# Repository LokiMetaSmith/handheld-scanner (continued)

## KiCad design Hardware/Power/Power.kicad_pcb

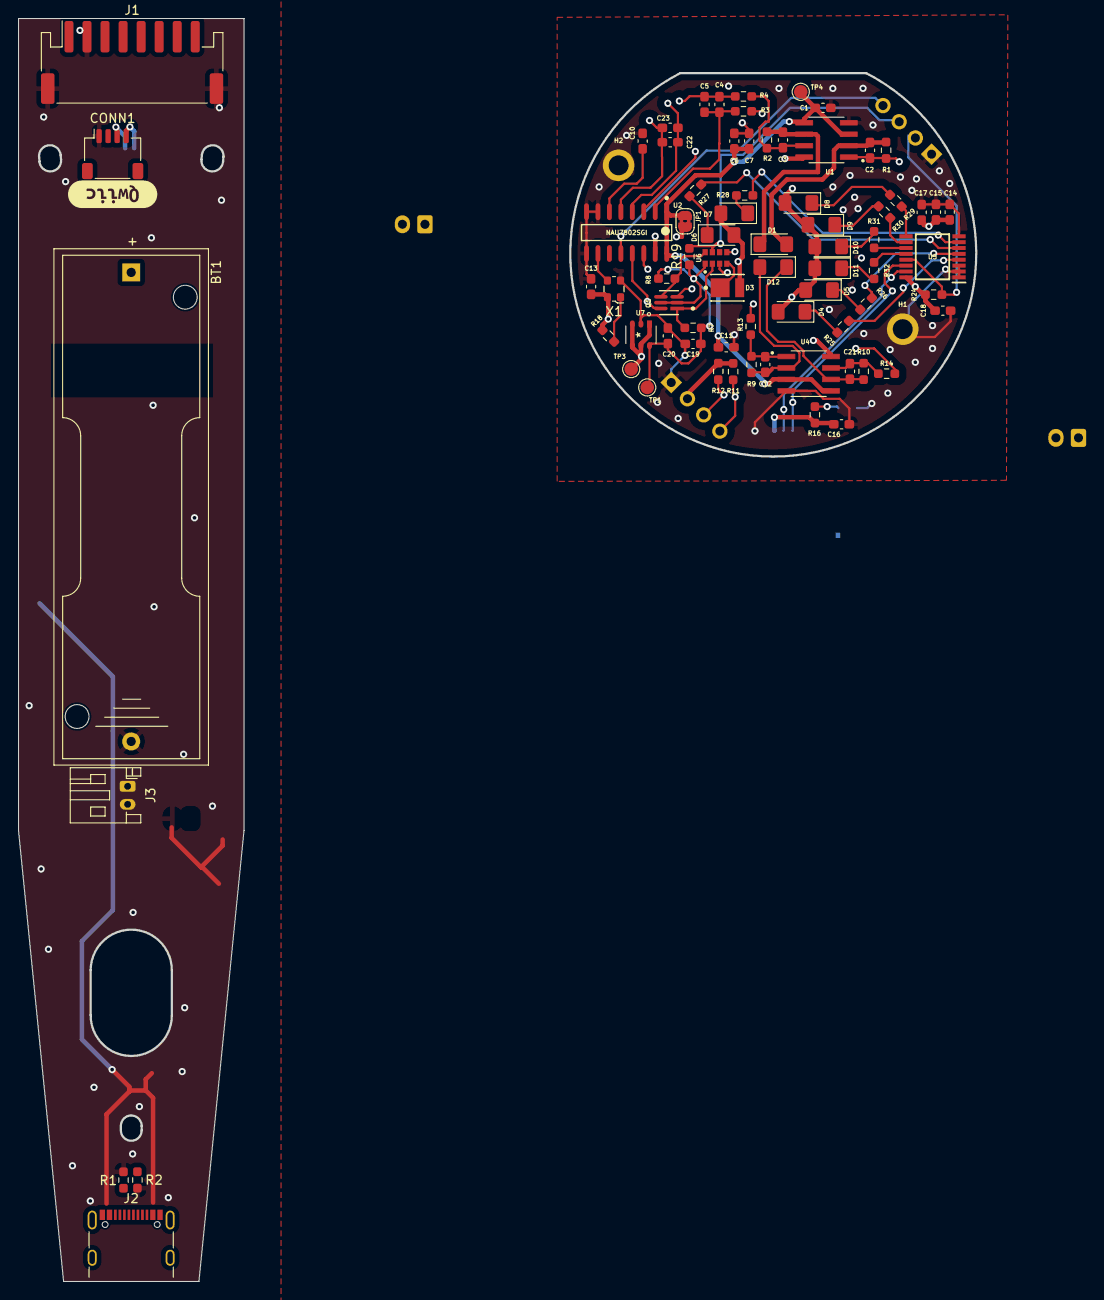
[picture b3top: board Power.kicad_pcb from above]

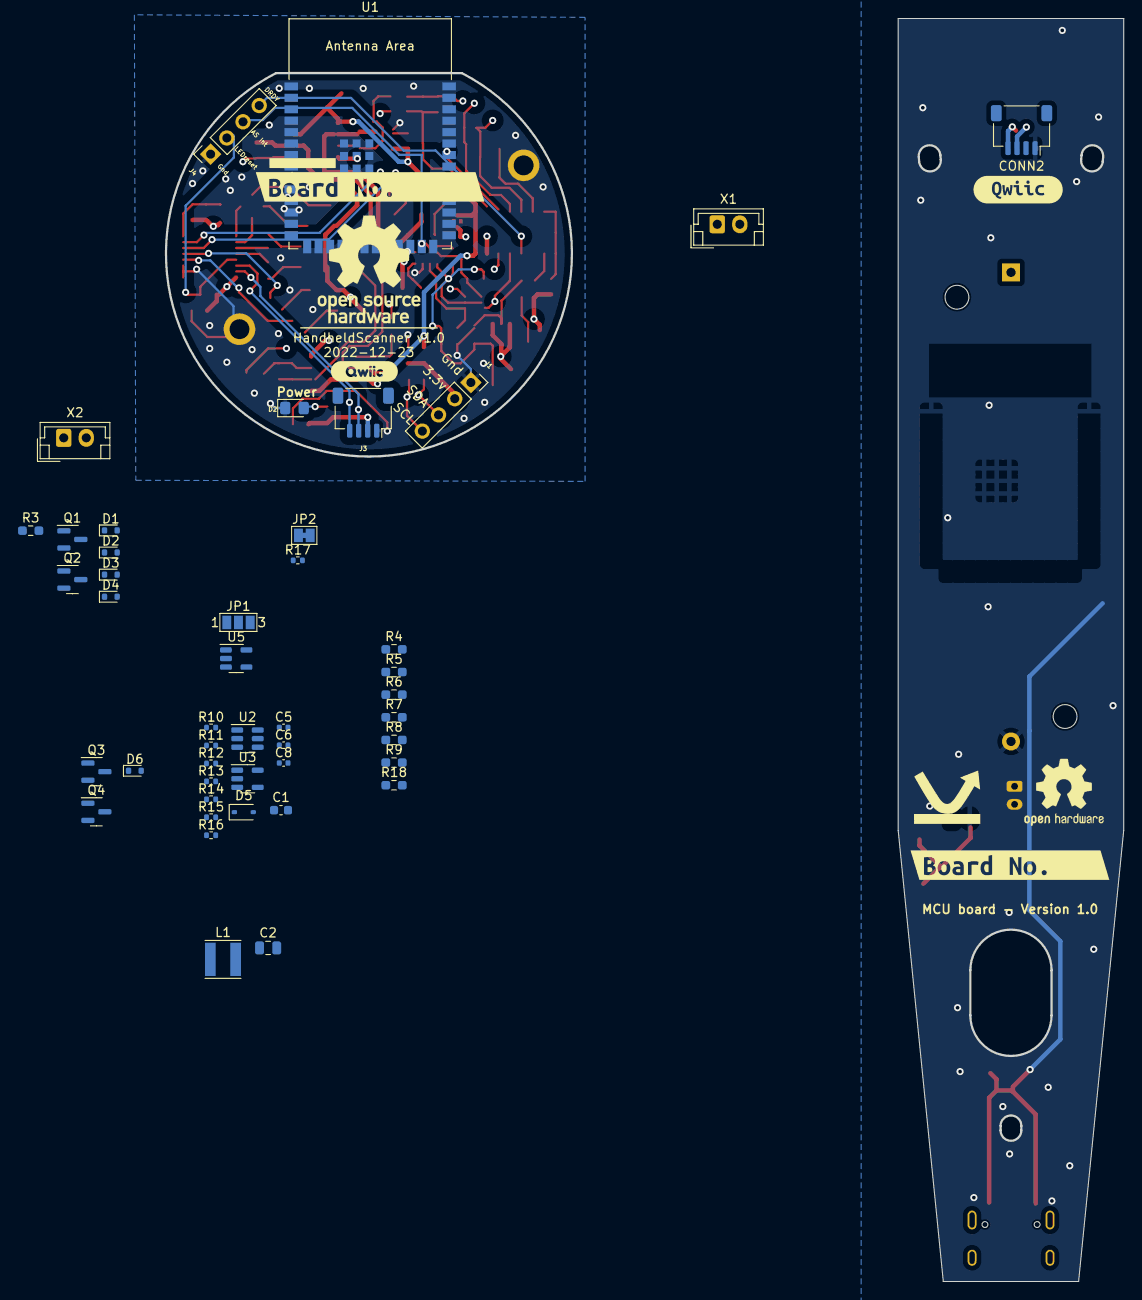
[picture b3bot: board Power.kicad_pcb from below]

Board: 4 copper layers, 106.2 x 140.0 mm, 131 parts (53 on the bottom side), 33 nets.

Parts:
BT1: Battery; BatteryHolder_Keystone_2460_1xAA
C1, C11, C16, C18: 100nF; C_0603_1608Metric_Pad1.08x0.95mm_HandSolder
C1#2: 2u; C_0603_1608Metric
C2, C3, C12, C21: 51pF; C_0603_1608Metric_Pad1.08x0.95mm_HandSolder
C2#2: 4.7u; C_0805_2012Metric
C4, C22: 47nF; C_0603_1608Metric_Pad1.08x0.95mm_HandSolder
C5, C23: 100pF; C_0603_1608Metric_Pad1.08x0.95mm_HandSolder
C5#2: 6.8p; C_0402_1005Metric
C6: 1uF; C_0603_1608Metric_Pad1.08x0.95mm_HandSolder
C6#2: 0.01u; C_0402_1005Metric
C7, C10, C13, C20: 0.1uF; C_0603_1608Metric_Pad1.08x0.95mm_HandSolder
C8: 0.1u; C_0402_1005Metric
C14, C15, C19: 10uF; C_0603_1608Metric_Pad1.08x0.95mm_HandSolder
C17: 22uF; C_0603_1608Metric_Pad1.08x0.95mm_HandSolder
CONN1, CONN2: STEMMA_I2C_QT; JST_SH_SM04B-SRSS-TB_1x04-1MP_P1.00mm_Horizontal
D1, D12: 0090-3111-185; D_1206_3216Metric_Pad1.42x1.75mm_HandSolder
D1#2, D2#2, D3#2, D4#2, D6#2: BAS516; D_SOD-523
D2: POWER LED; LED_0805_2012Metric_Pad1.15x1.40mm_HandSolder
D3: EAHC2835WD6; Everlight-EAHC2835WD6-MFG
D4: 855nm; LED_1206_3216Metric_Pad1.42x1.75mm_HandSolder
D5: 940nm; LED_1206_3216Metric_Pad1.42x1.75mm_HandSolder
D5#2: 3.3v_TVS; D_SOD-323
D6: 1050nm; LED_1206_3216Metric_Pad1.42x1.75mm_HandSolder
D7: 1300nm; LED_1206_3216Metric_Pad1.42x1.75mm_HandSolder
D8: 1460nm; LED_1206_3216Metric_Pad1.42x1.75mm_HandSolder
D9: 1550nm; LED_1206_3216Metric_Pad1.42x1.75mm_HandSolder
D10: 1650nm; LED_1206_3216Metric_Pad1.42x1.75mm_HandSolder
D11: 1720nm; LED_1206_3216Metric_Pad1.42x1.75mm_HandSolder
H1, H2: MountingHole; MountingHole_2.2mm_M2_ISO7380_Pad
J1: Conn_01x08_MountingPin; JST_PH_S8B-PH-SM4-TB_1x08-1MP_P2.00mm_Horizontal
J1#2: I2C ThroughHole; PinSocket_1x04_P2.54mm_Vertical
J2: USB_C_Receptacle_USB2.0; USB_C_Receptacle_GCT_USB4105-xx-A_16P_TopMnt_Horizontal
J3: Conn_01x02_Male; JST_PH_S2B-PH-K_1x02_P2.00mm_Horizontal
J3#2: I2C; JST_SH_SM04B-SRSS-TB_1x04-1MP_P1.00mm_Horizontal
J4: Interface; PinSocket_1x04_P2.54mm_Vertical
JP1: Jumper_2_Bridged; SolderJumper-2_P1.3mm_Bridged2Bar_RoundedPad1.0x1.5mm
JP1#2: SolderJumper_3_Open; SolderJumper-3_P1.3mm_Open_Pad1.0x1.5mm_NumberLabels
JP2: SolderJumper_2_Bridged; SolderJumper-2_P1.3mm_Bridged_Pad1.0x1.5mm
L1: 2.2uH; L_Taiyo-Yuden_MD-4040
LOGO1: OSHW-Logo_11.4x12mm_SilkScreen
LOGO2: PlasticScannerLogo
OSH logo: OSHW-Logo2_9.8x8mm_SilkScreen
PlasticScannerLogo: PlasticScannerLogo
Q1: BSS138DW-7-F; Diodes_Inc._-_BSS138DW-7-F-A
Q1#2, Q3: BC818; SOT-23
Q2, Q4: AO3401A; SOT-23
R1, R2#2: 5.1k; R_0603_1608Metric_Pad0.98x0.95mm_HandSolder
R1#2, R2, R9, R10: 240k; R_0603_1608Metric_Pad0.98x0.95mm_HandSolder
R3, R4, R13, R14: 301; R_0603_1608Metric_Pad0.98x0.95mm_HandSolder
R3#2, R18, R24: 1k; R_0603_1608Metric_Pad0.98x0.95mm_HandSolder
R4#2, R8#2, R18#2: 100k; R_0603_1608Metric_Pad0.98x0.95mm_HandSolder
R5, R7, R7#2, R8, R11, R12, R19: 10k; R_0603_1608Metric_Pad0.98x0.95mm_HandSolder
R6: 220k; R_0603_1608Metric_Pad0.98x0.95mm_HandSolder
R9#2: 220; R_0603_1608Metric_Pad0.98x0.95mm_HandSolder
R10#2, R11#2: 15K; R_0402_1005Metric
R12#2, R13#2: 27; R_0402_1005Metric
R14#2: 10K; R_0402_1005Metric
R15: 680k; R_0402_1005Metric
R16, R26, R29, R30: 150; R_0603_1608Metric_Pad0.98x0.95mm_HandSolder
R16#2: 150K; R_0402_1005Metric
R17: 5.1k; R_0402_1005Metric
R25: 56; R_0603_1608Metric_Pad0.98x0.95mm_HandSolder
R27, R28: 240; R_0603_1608Metric_Pad0.98x0.95mm_HandSolder
R31: 40; R_0603_1608Metric_Pad0.98x0.95mm_HandSolder
R32: 130; R_0603_1608Metric_Pad0.98x0.95mm_HandSolder
TP1: Test_1.8V; TestPoint_Pad_D1.5mm
TP3: Test_3.3V; TestPoint_Pad_D1.5mm
TP4: Test_2.5V; TestPoint_Pad_D1.5mm
U1, U4: OPA2376xxD; SOIC127P599X175-8N
U1#2: ESP32-S3-WROOM-1
U2: NAU7802SGI; Nuvoton-NAU7802SGI
U2#2: SN65220; SOT-23-6
U3: TLV62569DBV; SOT-23-5
U5: TLC59208FIPWR; SOP65P640X120-16N
U5#2: MCP73811T-420I-OT; SOT-23-5
U6: AS7341-DLGT; PSON80P310X200X110-8N
U7: AP7312-1833W6-7
X1: 4.9152 MHz; Oscillator_SMD_ECS_2520MV-xxx-xx-4Pin_2.5x2.0mm
X1#2, X2: CON_JST_PH_2PIN_MTPH2; JST_EH_B2B-EH-A_1x02_P2.50mm_Vertical
kibuzzard-6398DD41: G***; kibuzzard-6398DD41
kibuzzard-639881D9: G***; kibuzzard-639881D9
kibuzzard-6346913B: G***; kibuzzard-6346913B
kibuzzard-63988507, kibuzzard-63988507#2: G***; kibuzzard-63988507

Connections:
3.3V: CONN1.2 (V+), CONN2.2 (V+), J1.1, U1#2.2 (3V3)
+3V3: C5#2.1, C6#2.1, C8.1, C13.1, C14.2, C15.2, C16.2, C17.1, C18.1, D3.2 (ANODE), D4.2 (A), D5.2 (A), D5#2.1 (A1), D6.2 (A), D7.2 (A), D8.2 (A), D9.2 (A), D10.2 (A), D11.2 (A), J1#2.2, J3#2.2, JP1.2 (B), L1.2, R11.1, R12.2, R14#2.2, R15.2, R16.1, R18.2, R24.2, TP3.1, U1.8 (V+), U2.15 (DVDD), U4.8 (V+), U5.16 (VCC), U7.1 (OUT2), U7.3 (EN2), U7.4 (EN1), U7.5 (IN), X1.4 (VDD)
/D+: J2.A6 (D+), J2.B6 (D+), R10#2.1, R12#2.1, U2#2.1, U2#2.6 (A)
/D-: J2.A7 (D-), J2.B7 (D-), R11#2.2, R13#2.1, U2#2.3, U2#2.4 (B)
/EN: C1#2.2, R14#2.1, U1#2.3 (EN)
/KeepAlive: D4#2.2 (A), U1#2.39 (GPIO1/TOUCH1/ADC1_CH0)
/SCL: CONN1.4 (SCL), CONN2.4 (SCL)
/SDA: CONN1.3 (SDA), CONN2.3 (SDA)
/Switched_Power: C2#2.1, D6#2.1 (K), Q4.2 (S), U3.1 (EN), U3.4 (VIN)
/Trigger: JP1#2.3 (B), U1#2.38 (GPIO2/TOUCH2/ADC1_CH1)
/Trigger_Wake_Up/VBAT: BT1.1 (+), J3.1, Q2.2 (S), R4#2.1, R5.2, U5#2.3 (VBAT), X1#2.2, X2.2
/USB_D+: R12#2.2, U1#2.14 (GPIO20/U1CTS/ADC2_CH9/CLK_OUT1/USB_D+)
/USB_D-: R13#2.2, U1#2.13 (GPIO19/U1RTS/ADC2_CH8/CLK_OUT2/USB_D-)
GND: BT1.2 (-), C1.1, C1#2.1, C2#2.2, C6.1, C6#2.2, C7.1, C8.2, C10.1, C11.1, C13.2, C14.1, C15.1, C16.1, C17.2, C18.2, C19.1, C20.1, CONN1.1 (GND), CONN2.1 (GND), D2.1 (K), D5#2.2 (A2), H1.1, H2.1, J1.2, J1.MP (MountPin), J1#2.1, J3.2, J3#2.1, J4.1, R1.2, R2#2.2, R6.1, R8#2.1, R10#2.2, R11#2.1, R16#2.1, R17.1, U1.4 (V-), U1#2.1 (GND), U1#2.40 (GND), U1#2.41 (GND), U2.7 (REFN), U2.8 (AVSS), U2.9 (DVSS), U2#2.2 (GND), U2#2.5 (GND), U3.2 (GND), U4.4 (V-), U5.1 (A0), U5.2 (A1), U5.3 (A2), U5.8 (GND), U5#2.2 (VSS), U6.3 (GND), U6.5 (PGND), U7.2 (GND), X1.2 (GND)
unnamed: D1#2.2 (A), JP1#2.1 (A)
unnamed: D1#2.1 (K), JP2.2 (B), R3#2.1
unnamed: D2#2.1 (K), JP2.1 (A)
unnamed: D3#2.2 (A), R7#2.1
unnamed: D3#2.1 (K), Q3.1 (B), R8#2.2, R9#2.2
unnamed: D4#2.1 (K), R9#2.1
unnamed: J2.A5 (CC1), R2#2.1
unnamed: J2.B5 (CC2), R1.1
unnamed: J2.A1 (GND), J2.A12 (GND), J2.B1 (GND), J2.B12 (GND)
unnamed: JP1#2.2 (C), X1#2.1
unnamed: Q1#2.1 (B), R3#2.2
unnamed: Q1#2.3 (C), R5.1
unnamed: Q1#2.2 (E), R6.2, R7#2.2
unnamed: Q2.3 (D), Q4.3 (D), X2.1
unnamed: Q2.1 (G), Q3.3 (C), R4#2.2
unnamed: C5#2.2, R15.1, R16#2.2, U3.5 (FB)
unnamed: L1.1, U3.3 (SW)
unnamed: R17.2, U5#2.5 (PROG)
USB_pwr: D2#2.2 (A), D6#2.2 (A), J2.A4 (VBUS), J2.A9 (VBUS), J2.B4 (VBUS), J2.B9 (VBUS), Q4.1 (G), R18#2.2, U5#2.1 (CEN), U5#2.4 (VDD)

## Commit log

2022-12-15 added recommended crystal layout to board
2023-06-06 Initial conversion and cleanup from a feather to an esp32s3
    added USB power
    Added switching 3.6-5v regulator
    updated schematic ground to use built in kicad libraries
    updated partially broken library references to eagle lib files
    added circuit simulator of trigger and wakeup simulation
2023-10-03 added footprint for MTSM2601SMF1-100
2023-10-03 removed defunct 3d model from MTSM2601SMF1-100 Signed-off-by: lokimetasmith <lokimail@gmail.com>
2023-10-30 lots of changes, added footprints, fixed broken schemaitcs, fixed kicad 7.0 issues
2023-10-30 second pass on controller rework
2023-11-01 updated routing on control board, added led pcb template
2023-11-10 added linear regulator for reference voltage
2023-11-10 added options for using internal adc, external adc, or 3.3v
2023-11-10 updated pcb silkscreen date
2023-11-20 updated schematic, and layout, updated bom, fully converted to 3.3v for Voltage input only
2023-11-20 updated red power led to a common lower value, dimmer power led shouldn't be an issue
2023-11-20 added missing QUICC connector
2023-11-21 added decoupling capactitors, added footprint for 3d model, need to verify new footprint
2023-11-22 cleared all DRC errors
2023-11-27 as ordered 11/27/2023 from JLCPCB
    Updated silk on RoundScanner, minor changes,
    major changes on control board, cleaned up foot prints, nudged parts around
    control board not ready for release yet
2024-05-27 Initial lilyGo-T-RGB commit
